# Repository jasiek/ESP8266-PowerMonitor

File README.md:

# ESP8266-PowerMonitor

See this project on <a href="https://kitspace.org/boards/github.com/jasiek/esp8266-powermonitor/"></img></a>

Uses [Lets Control It/ESP Easy](https://www.letscontrolit.com/).

## Programming

Download the latest [ESP Easy Mega release](https://github.com/letscontrolit/ESPEasy/releases).

Install [esptool.py](https://github.com/espressif/esptool). Hook up a USB-to-serial adapter to the board.

Short `_PROG` & `GND` and press RESET.

Find the right firmware file (`normal_ESP8266_4M1M`) and run:

```
$ esptool.py --port /dev/cu.usbserial-14120 --baud 115200 write_flash 0 ESP_Easy_mega_20200516_normal_ESP8266_4M1M.bin
```

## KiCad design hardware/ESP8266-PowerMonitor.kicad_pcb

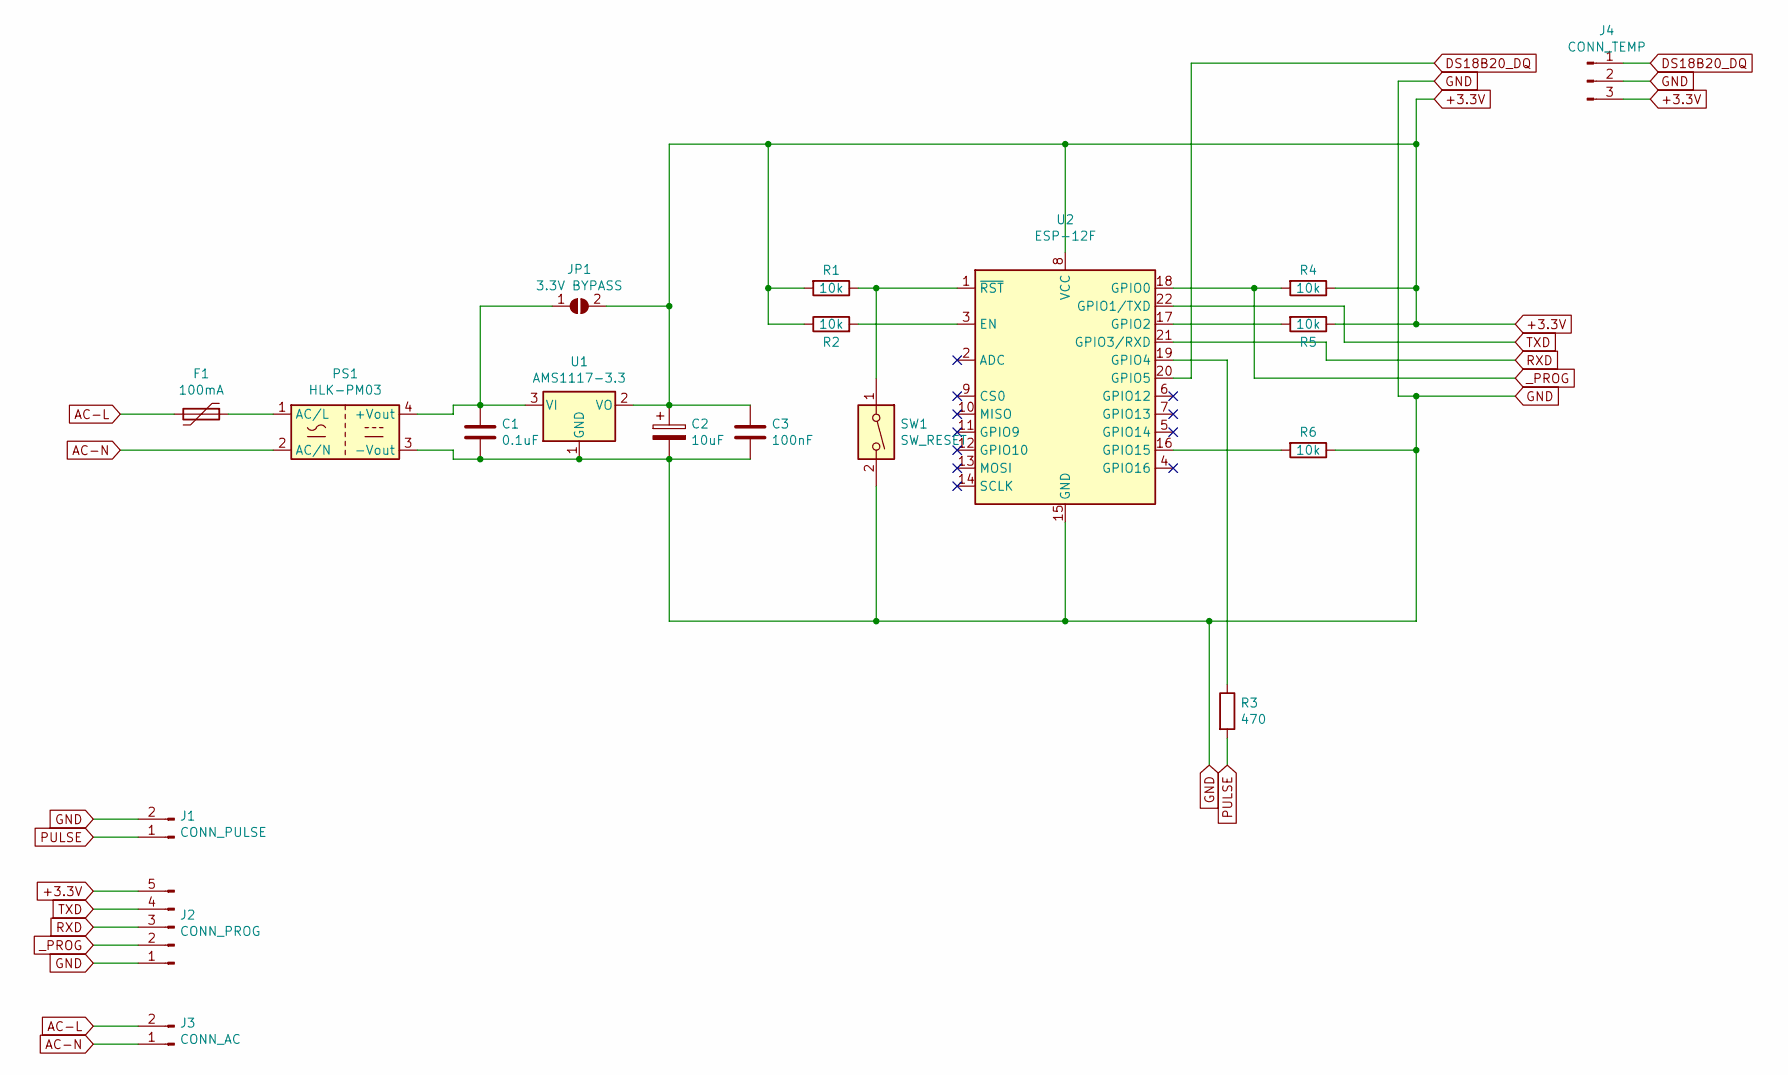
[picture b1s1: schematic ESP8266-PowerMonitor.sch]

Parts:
C1: 0.1uF; C_1206_3216Metric_Pad1.42x1.75mm_HandSolder
C2: 10uF; CP_Elec_4x5.3
C3: 100nF; C_1206_3216Metric_Pad1.42x1.75mm_HandSolder
F1: 100mA; Fuse_1206_3216Metric_Pad1.42x1.75mm_HandSolder
J1: CONN_PULSE; PinHeader_1x02_P2.54mm_Vertical
J2: CONN_PROG; PinHeader_1x05_P2.54mm_Vertical
J3: CONN_AC; TerminalBlock_bornier-2_P5.08mm
J4: CONN_TEMP; PinHeader_1x03_P2.54mm_Vertical
JP1: 3.3V BYPASS; SolderJumper-2_P1.3mm_Open_TrianglePad1.0x1.5mm
PS1: HLK-PM03; Converter_ACDC_HiLink_HLK-PMxx
R1, R2, R4, R5, R6: 10k; R_1206_3216Metric_Pad1.42x1.75mm_HandSolder
R3: 470; R_1206_3216Metric_Pad1.42x1.75mm_HandSolder
SW1: SW_RESET; SW_Push_1P1T_NO_6x6mm_H9.5mm
U1: AMS1117-3.3; SOT-223-3_TabPin2
U2: ESP-12F; ESP-12E

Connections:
+3.3V: C2.1, C3.1, J2.5, J4.3, JP1.2 (B), R1.2, R2.1, R4.1, R5.1, U1.2 (VO), U2.8 (VCC)
AC-L: F1.2, J3.2
AC-N: J3.1, PS1.2 (AC/N)
DS18B20_DQ: J4.1, U2.20 (GPIO5)
GND: C1.2, C2.2, C3.2, J1.2, J2.1, J4.2, PS1.3 (-Vout), R6.1, SW1.2, U1.1 (GND), U2.15 (GND)
unnamed: C1.1, JP1.1 (A), PS1.4 (+Vout), U1.3 (VI)
unnamed: F1.1, PS1.1 (AC/L)
unnamed: R1.1, SW1.1, U2.1 (~RST)
unnamed: R2.2, U2.3 (EN)
unnamed: R3.1, U2.19 (GPIO4)
unnamed: R5.2, U2.17 (GPIO2)
unnamed: R6.2, U2.16 (GPIO15)
PULSE: J1.1, R3.2
RXD: J2.3, U2.21 (GPIO3/RXD)
TXD: J2.4, U2.22 (GPIO1/TXD)
_PROG: J2.2, R4.2, U2.18 (GPIO0)

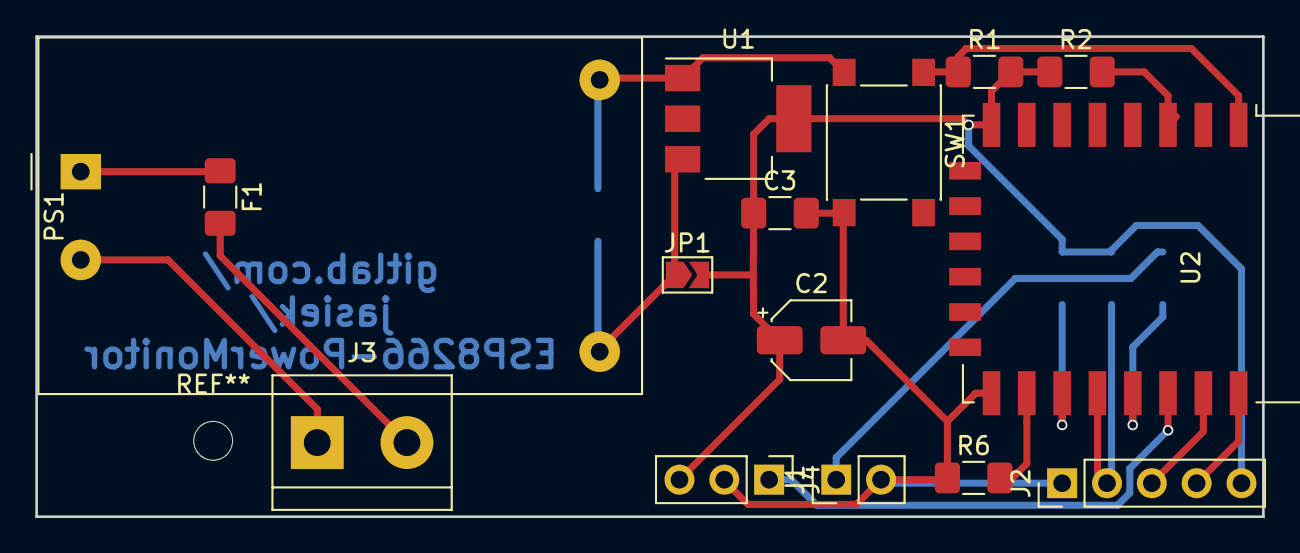
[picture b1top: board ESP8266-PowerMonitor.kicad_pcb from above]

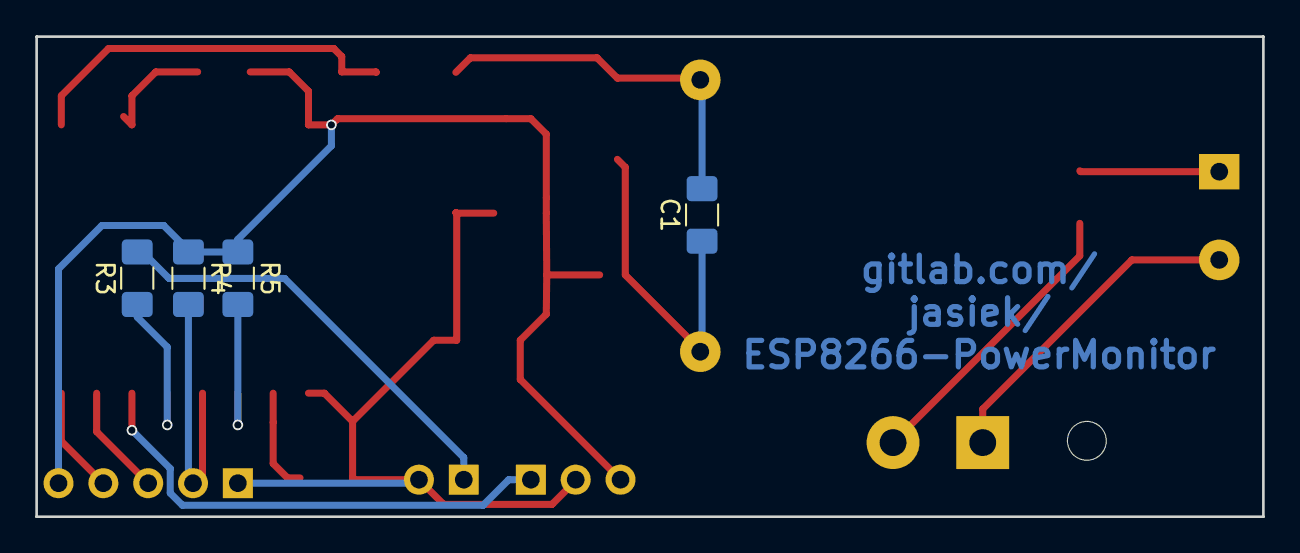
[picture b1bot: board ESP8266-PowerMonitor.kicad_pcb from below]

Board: 2 copper layers, 69.5 x 27.2 mm, 19 parts (4 on the bottom side), 16 nets.

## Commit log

2015-12-01 Initial commit.
2015-12-01 .gitignore and settings.
2015-12-01 I need to actually hook this up to do any testing.
2015-12-05 Each pulse is at least 80ms. We can measure those now.
2015-12-05 These variables don't really need to be volatile, I think.
2015-12-07 Started sketching PCBs etc.
2015-12-11 Added the rest of wires + 1wire bus.
2015-12-11 A few updates to the scheamtics.
2015-12-13 Added DS18B20 temperature sensor and a PIR sensor.
2015-12-13 Added reporting, let's see how well this works.
2015-12-14 Added error count tracking to see how many transfers are unsuccessful.
2015-12-14 Almost done with the board.
2015-12-15 Production prints.
2015-12-27 statsd class shamelessly ripped off from https://github.com/zackkitzmiller/statsd-arduino
2015-12-28 StatsD client works with the ESP8266.
2015-12-28 Report temperature, movement and power consumption - initial testing.
2015-12-29 Periodic reporting now works with statsd.
2015-12-29 When we get disconnected from the network, attempt to reconnect before sending out data.
2015-12-29 StatsD class can now report fractional values.
2015-12-30 Disable the access point that gets enabled by default.
2015-12-30 Report RSSI and voltage.
2015-12-30 Report RSSI and voltage. RSSI reported has to be a positive value, otherwise statsd thinks we're dealing with deltas.
2015-12-30 Node name is now set correctly, to the mac address of the device. RSSI and temperature are reported by first setting the value to 0 to allow for negative values. RSSI is reported as a negative value.
2015-12-31 Movement counter as a gauge, when setting a gauge to zero, use 0 as int.
2016-01-01 Don't need multiple access points at the moment.
2016-01-01 Send a dummy packet indicating that we have indeed sent packets for debugging purposes.
2016-01-01 Error signalling using an LED on GPIO16.
2016-01-01 Respond to MDNS queries.
2016-01-01 Better pulse length measurement.
2016-01-01 Fixed a few typos.
2016-01-01 Updated schematics & PCB.
2016-01-02 EM interference should no longer prevent the 1 wire bus from working.
2016-01-03 Added a web server on port 80 that returns json. Used tickers rather than a loop with a delay to gather and send data.
2016-01-03 Got rid of unnecessary delays.
2016-01-03 Tidying up.
2016-01-04 Updated netlist and footprints.
2016-01-05 Change the reporting interval to 60 seconds.
2016-01-06 Changed 4.7k resistor to 2.2k to facilitate greater 1 wire length.
2016-01-06 Updated .gitignore
2016-01-06 Improved, complete PCB, pre-panelized.
2016-01-06 Removed old plot, added a new, panelized plot and PCB.
2016-01-06 A few pictures.
2016-01-08 Generated new top-left corner aligned PCB and drill files.
2016-01-11 Output is returned in Wh, added a few settings.
2016-01-23 Use counters instead of gauges.
2016-01-26 Start using my statsdclient.
2016-01-27 Chain statsd metrics, bump resolution to 12 bits (why not?).
2016-03-20 Instead of statsd, report everything via HTTP.
2016-03-26 Fixed HTTP client, requires the use of WiFiMulti...
2016-03-26 Halt the ticker when making a HTTP request.
2016-03-28 Using ticket callbacks doesn't work for some reason.
2016-03-30 Migrated project to PlatformIO.
2016-03-30 Added README.
2016-04-06 Added references to installable libraries.
2016-08-29 Updated user-agent to something recognizable, updated gitignore.
2016-09-12 Add MQTT support.
2016-10-02 Count pulses, not kWh.
2016-10-02 Modified client name for MQTT
2016-10-03 Force a reset after reporting results, there's an issue with lock up of some sort.
2016-10-04 Report only once per cycle.
2016-10-05 ESP.restart() doesn't work reliably, got rid of it. Removed ticker which wasn't used anywhere. Added more verbose reporting of what the device is up to atm.
2016-10-06 ESP.restart() fix.
    https://github.com/esp8266/Arduino/issues/1017#issuecomment-200605576
    https://github.com/esp8266/Arduino/blob/master/doc/faq/readme.md#i-have-observed-a-case-when-esprestart-doesnt-work-what-is-the-reason-for-that
2016-10-06 Add GIT_REVISION to the welcome message and to the user agent.
2016-10-07 Print out the measured pulse width, for debugging purposes.
2016-10-07 We need a define to ensure we can send packets out from this node.
2016-11-23 MQTT messages should be retained.
2016-12-11 Use MQTT as the transport mechanism.
2016-12-17 Set the client name to something more meaningful.
2017-02-06 Renamed main file to cpp
2017-02-06 Quick hack to enable remote update shim and basic functionality.
2017-02-06 Temporary fix.
2017-02-06 Hardcode pulse length to 35 msec for now.
2017-02-16 Tweaks to make everything work with metering.
2017-02-23 Updated reference to point to the latest version of metering.
2017-07-02 Updated source to work with the latest version of metering.
2017-07-02 Another batch of fixes to platformio.ini
2018-07-14 We now include a timestamp in the payload.
2018-07-15 Bumped version of metering to 0.2.1 which fixes a few things.
2019-12-28 Bumped dependencies to the latest version of metering. Removed logic around classifying which power sensor is used - as long as there's a pulse < 90ms we will count it. Added ICACHE_RAM_ATTR attribut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
2019-12-28 Do not restart the sensor.
2020-04-24 Redesigned the board.
2020-04-27 * Reworked the board to use 0.5/1.3mm vias. * Added I2C to GPIO4/5 in case we want to use an OLED display. * Moved the pulse pin to GPIO2 (pulled up). * Re-orged the board to use fewer vias.
2020-04-27 Updated .gitignore.
2020-04-27 gh pages?
2020-05-25 Updated PCB, uses GPIO13 instead of GPIO2, which didn't work.
2020-05-25 Removed firmware files, no longer needed.
2020-05-25 Cleaned up pictures, updated README.
2020-05-25 Enable project on kitspace.org
2020-05-25 Further kitspace tweaks.
2020-06-25 Added a link to order a PCB.
2020-06-28 Revision 2 PCB done.
2020-06-28 Kitspace link
2020-07-07 Added PDF of the schematic.
